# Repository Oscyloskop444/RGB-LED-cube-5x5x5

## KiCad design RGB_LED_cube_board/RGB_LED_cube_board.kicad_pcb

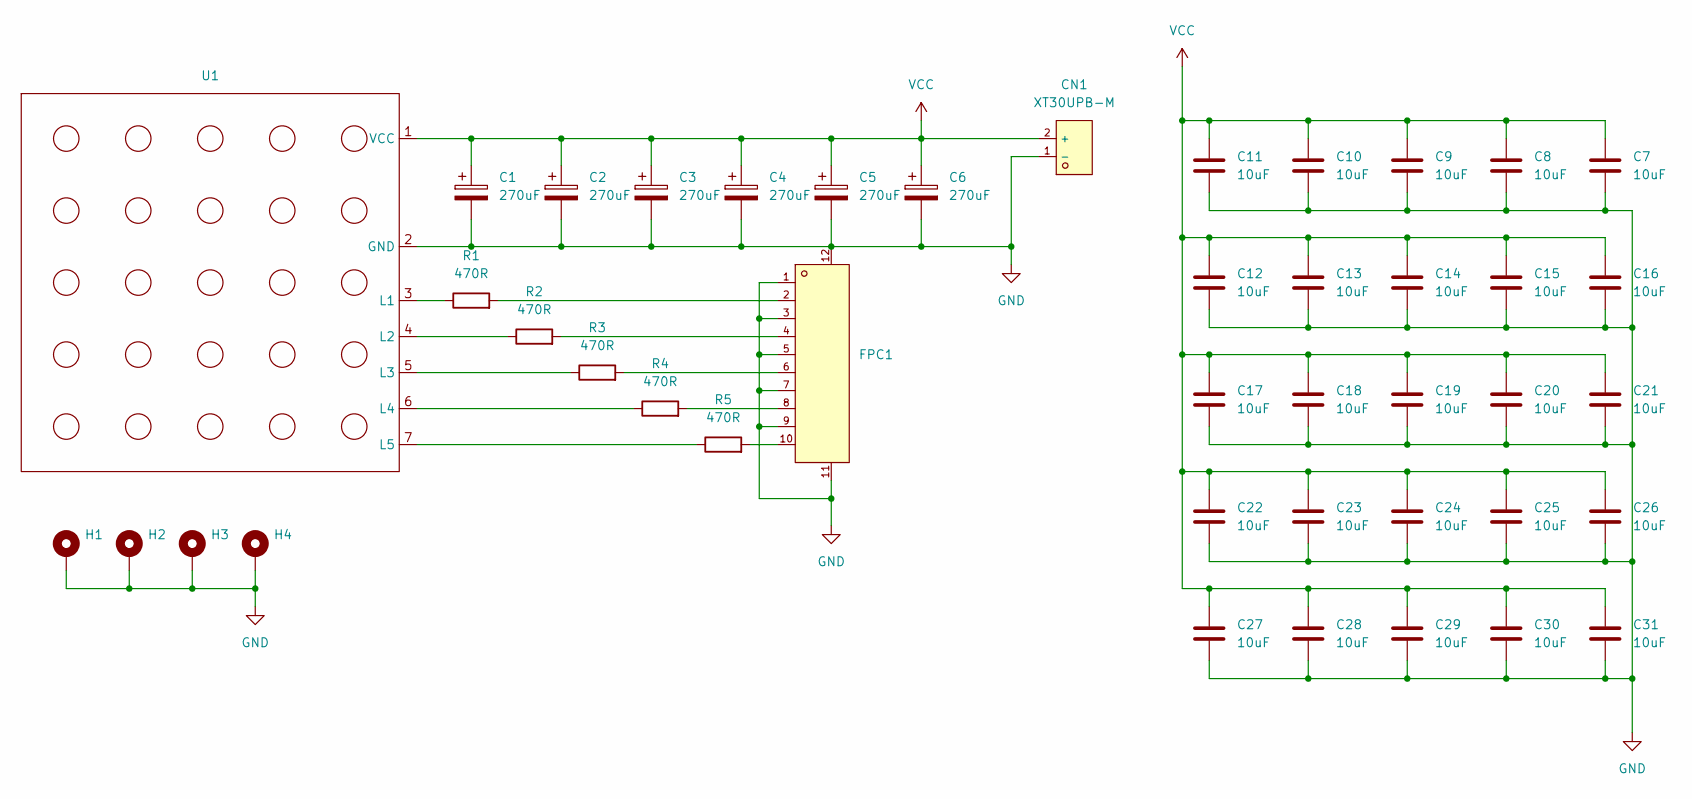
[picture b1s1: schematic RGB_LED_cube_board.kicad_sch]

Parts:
C1, C2, C3, C4, C5, C6: 270uF; C_Radial_D6.3mm_H11.0mm_P2.50mm
C7, C8, C9, C10, C11, C12, C13, C14, C15, C16, C17, C18, C19, C20, C21, C22, C23, C24, C25, C26, C27, C28, C29, C30, C31: 10uF; C_0603_1608Metric_Pad1.08x0.95mm_HandSolder
CN1: XT30UPB-M; C428721_CONN-TH_XT30UPB-M; LCSC C428721
FPC1: XW05202-100R-00; C2906114_FPC-SMD_10P-P0_50_HCTL_XW05202-100R-00; LCSC C2906114
H1, H2, H3, H4: MountingHole_Pad; MountingHole_3.2mm_M3_Pad_Via
R1, R2, R3, R4, R5: 470R; R_0402_1005Metric_Pad0.72x0.64mm_HandSolder
U1: LED_CUBE_RGB_5x5x5

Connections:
GND: C1.2, C2.2, C3.2, C4.2, C5.2, C6.2, C7.2, C8.2, C9.2, C10.2, C11.2, C12.2, C13.2, C14.2, C15.2, C16.2, C17.2, C18.2, C19.2, C20.2, C21.2, C22.2, C23.2, C24.2, C25.2, C26.2, C27.2, C28.2, C29.2, C30.2, C31.2, CN1.1 (-), FPC1.1, FPC1.3, FPC1.5, FPC1.7, FPC1.9, FPC1.11, FPC1.12, H1.1 (1_1), H2.1 (1_1), H3.1 (1_1), H4.1 (1_1), U1.2 (GND)
unnamed: FPC1.2, R1.2
unnamed: FPC1.4, R2.2
unnamed: FPC1.6, R3.2
unnamed: FPC1.8, R4.2
unnamed: FPC1.10, R5.2
unnamed: R1.1, U1.3 (L1)
unnamed: R2.1, U1.4 (L2)
unnamed: R3.1, U1.5 (L3)
unnamed: R4.1, U1.6 (L4)
unnamed: R5.1, U1.7 (L5)
VCC: C1.1, C2.1, C3.1, C4.1, C5.1, C6.1, C7.1, C8.1, C9.1, C10.1, C11.1, C12.1, C13.1, C14.1, C15.1, C16.1, C17.1, C18.1, C19.1, C20.1, C21.1, C22.1, C23.1, C24.1, C25.1, C26.1, C27.1, C28.1, C29.1, C30.1, C31.1, CN1.2 (+), U1.1 (VCC)

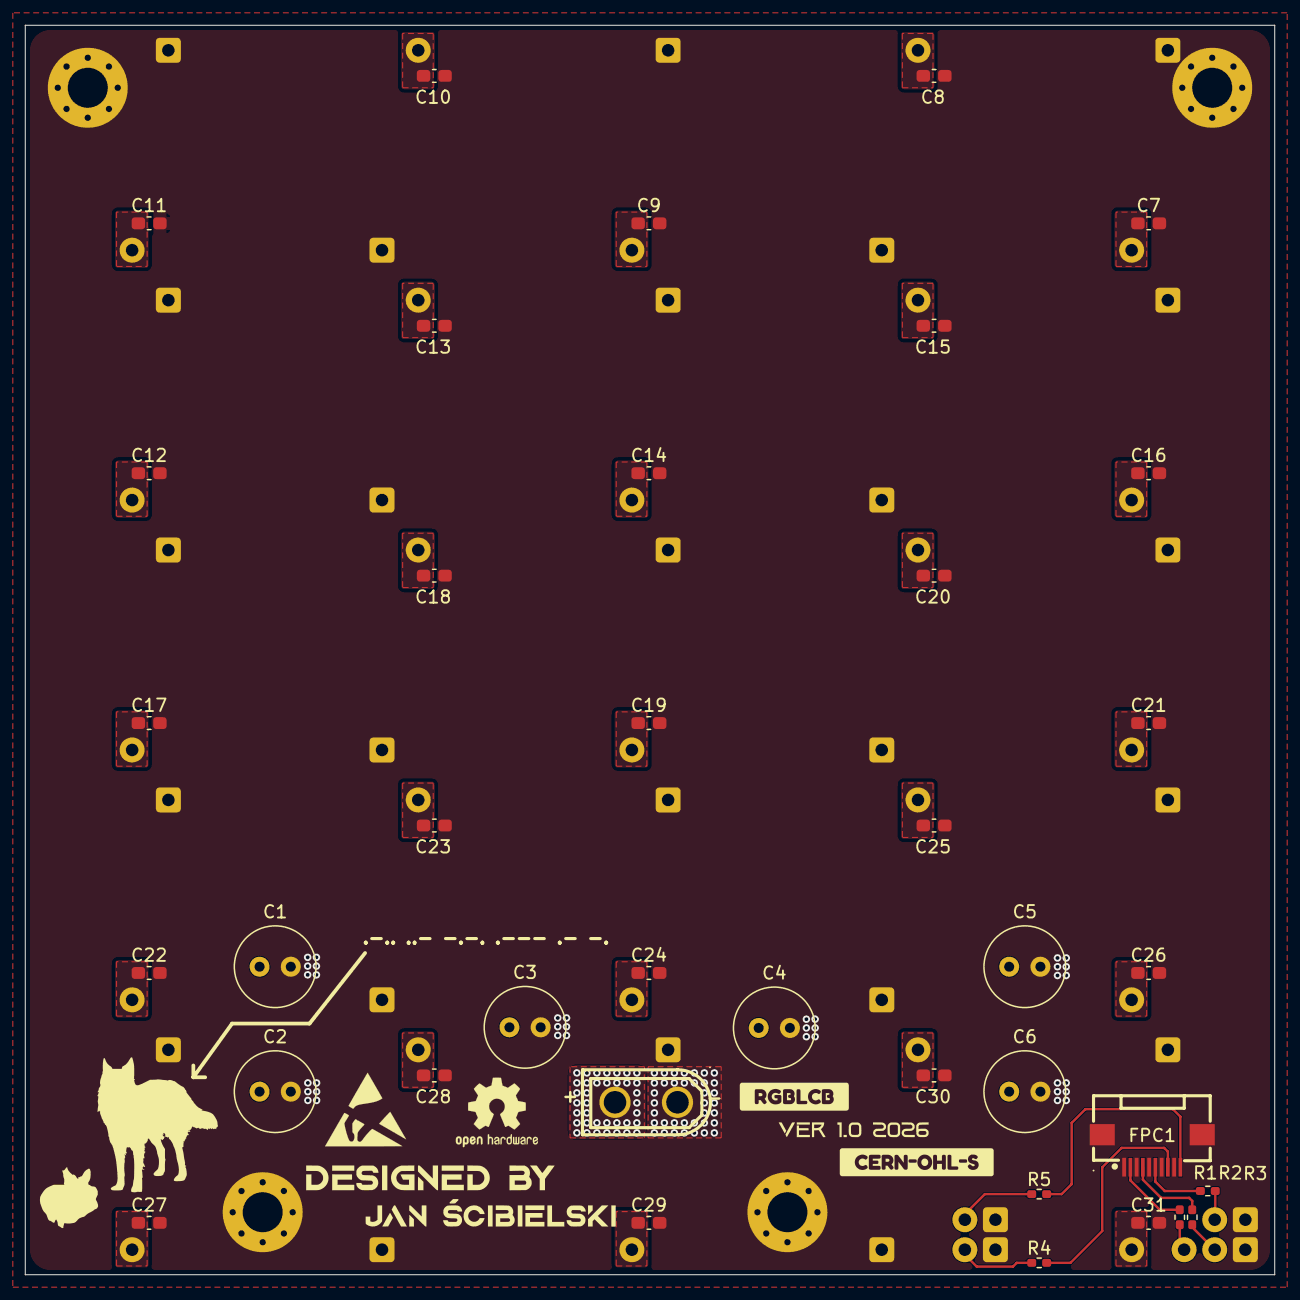
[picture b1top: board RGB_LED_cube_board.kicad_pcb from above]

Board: 2 copper layers, 100.0 x 100.0 mm, 45 parts (1 on the bottom side), 12 nets.

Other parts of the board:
kobee-studio-6AA9EF40: Kobee Studio; kobee-studio-6AA9EF40
kobee-studio-6AA92370: Kobee Studio; kobee-studio-6AA92370

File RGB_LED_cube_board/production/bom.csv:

Designator,Footprint,Quantity,Value,LCSC Part #
"C1, C2, C3, C4, C5, C6",C_Radial_D6.3mm_H11.0mm_P2.50mm,6,270uF,
"C10, C11, C12, C13, C14, C15, C16, C17, C18, C19, C20, C21, C22, C23, C24, C25, C26, C27, C28, C29, C30, C31, C7, C8, C9",0603,25,10uF,
CN1,C428721_CONN-TH_XT30UPB-M,1,XT30UPB-M,C428721
FPC1,C2906114_FPC-SMD_10P-P0_50_HCTL_XW05202-100R-00,1,XW05202-100R-00,C2906114
"R1, R2, R3, R4, R5",0402,5,470R,
U1,LED_CUBE_RGB_5x5x5,1,~,
